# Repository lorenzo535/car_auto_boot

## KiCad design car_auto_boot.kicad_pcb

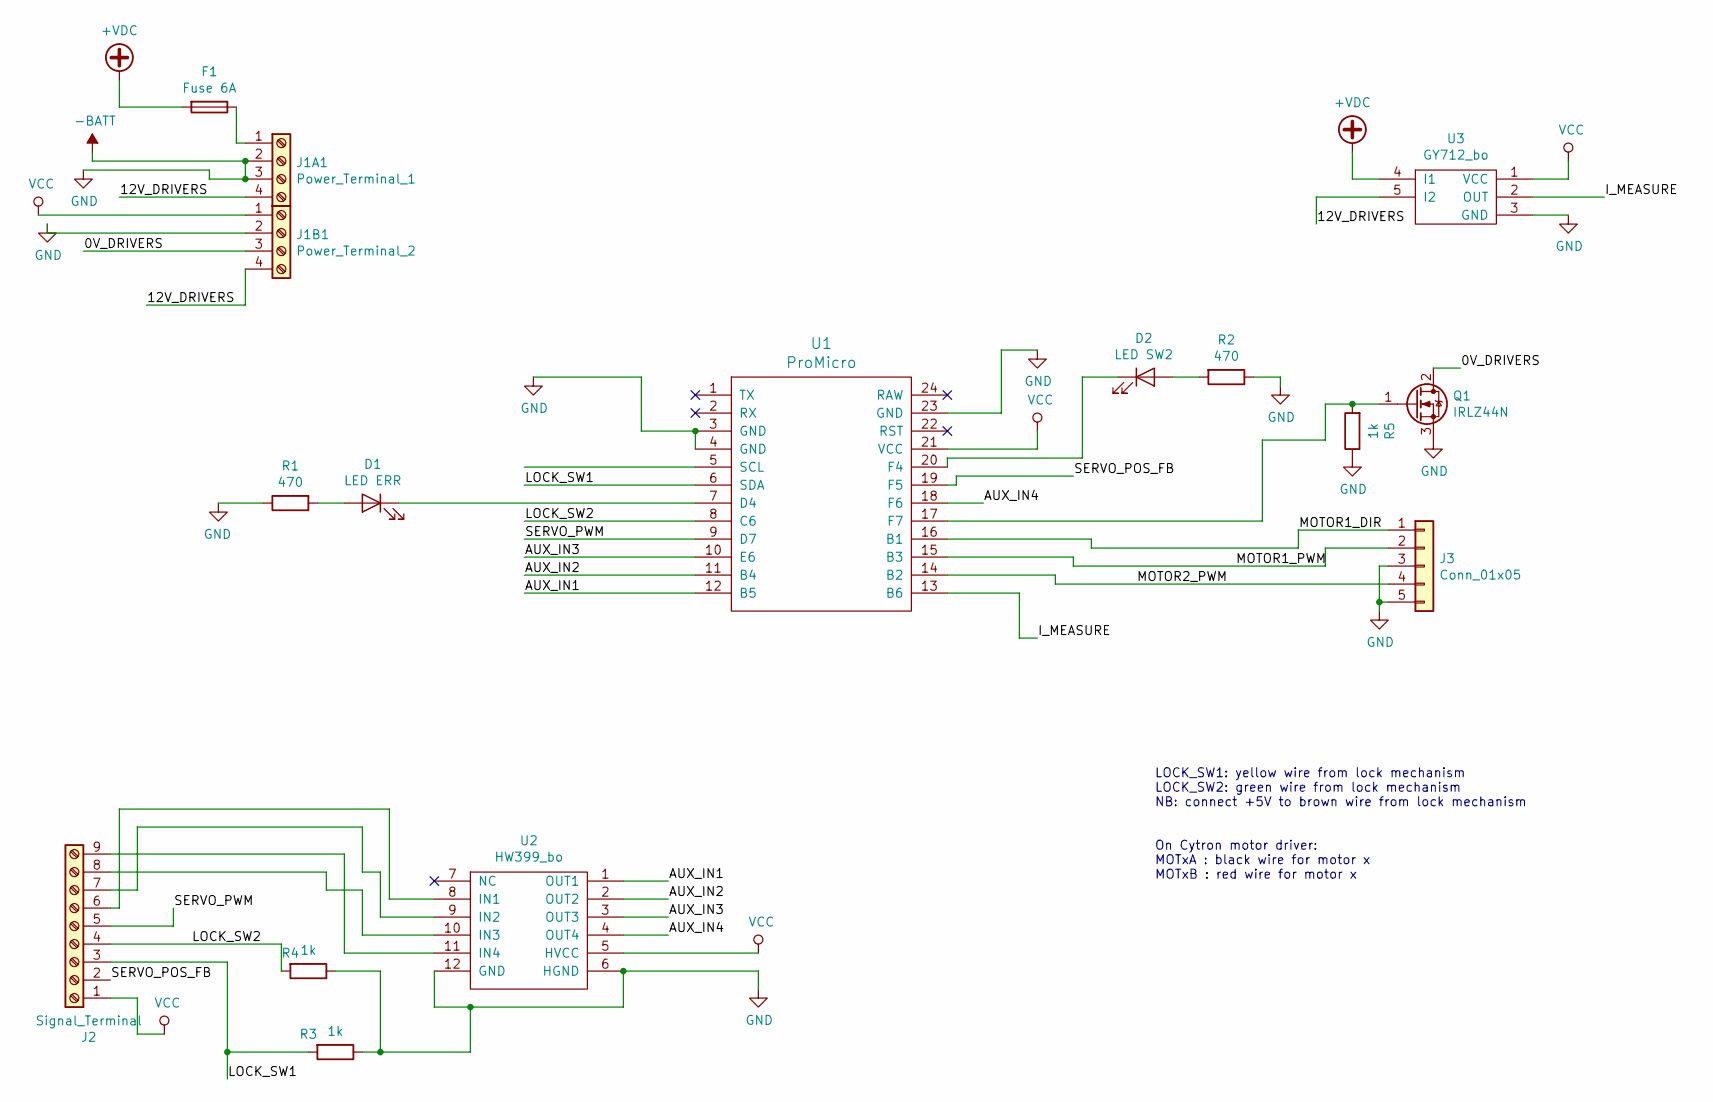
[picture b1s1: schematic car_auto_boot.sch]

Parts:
D1: LED ERR; LED_D3.0mm
D2: LED SW2; LED_D3.0mm
F1: Fuse 6A; Fuseholder5x20_horiz_SemiClosed_Casing10x25mm
J1A1: Power_Terminal_1; TerminalBlock_bornier-4_P5.08mm
J1B1: Power_Terminal_2; TerminalBlock_bornier-4_P5.08mm
J2: Signal_Terminal; TerminalBlock_Phoenix_MPT-2.54mm_9pol
J3: Conn_01x05; TerminalBlock_Phoenix_MPT-2.54mm_5pol
Q1: IRLZ44N; TO-220-3_Vertical
R1, R2: 470; R_Axial_DIN0207_L6.3mm_D2.5mm_P7.62mm_Horizontal
R3, R4, R5: 1k; R_Axial_DIN0207_L6.3mm_D2.5mm_P7.62mm_Horizontal
U1: ProMicro
U2: HW399_bo; HW399_BO
U3: GY712_bo; GY712_BO

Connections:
+VDC: F1.2, U3.4 (I1)
-BATT: J1A1.2, J1A1.3, J1B1.2, J3.3, J3.5, Q1.3 (S), R1.1, R2.1, R3.1, R4.1, R5.1, U1.3 (GND), U1.4 (GND), U1.23 (GND), U2.6 (HGND), U2.12 (GND), U3.3 (GND)
/0V_DRIVERS: J1B1.3, Q1.2 (D)
/12V_DRIVERS: J1A1.4, J1B1.4, U3.5 (I2)
/AUX_IN1: U1.12 (B5), U2.1 (OUT1)
/AUX_IN2: U1.11 (B4), U2.2 (OUT2)
/AUX_IN3: U1.10 (E6), U2.3 (OUT3)
/AUX_IN4: U1.18 (F6), U2.4 (OUT4)
/I_MEASURE: U1.13 (B6), U3.2 (OUT)
/LOCK_SW1: J2.3, R3.2, U1.6 (SDA)
/LOCK_SW2: J2.4, R4.2, U1.8 (C6)
/MOTOR1_DIR: J3.1, U1.16 (B1)
/MOTOR1_PWM: J3.2, U1.15 (B3)
/MOTOR2_PWM: J3.4, U1.14 (B2)
/SERVO_POS_FB: J2.2, U1.19 (F5)
/SERVO_PWM: J2.5, U1.9 (D7)
unnamed: D1.1 (K), U1.7 (D4)
unnamed: D1.2 (A), R1.2
unnamed: D2.1 (K), U1.20 (F4)
unnamed: D2.2 (A), R2.2
unnamed: F1.1, J1A1.1
unnamed: J2.6, U2.8 (IN1)
unnamed: J2.7, U2.9 (IN2)
unnamed: J2.8, U2.10 (IN3)
unnamed: J2.9, U2.11 (IN4)
unnamed: Q1.1 (G), R5.2, U1.17 (F7)
VCC: J1B1.1, J2.1, U1.21 (VCC), U2.5 (HVCC), U3.1 (VCC)

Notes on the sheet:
LOCK_SW1: yellow wire from lock mechanism LOCK_SW2: green wire from lock mechanism NB: connect +5V to brown wire from lock mechanism On Cytron motor driver: MOTxA : black wire for motor x MOTxB : red wire for motor x

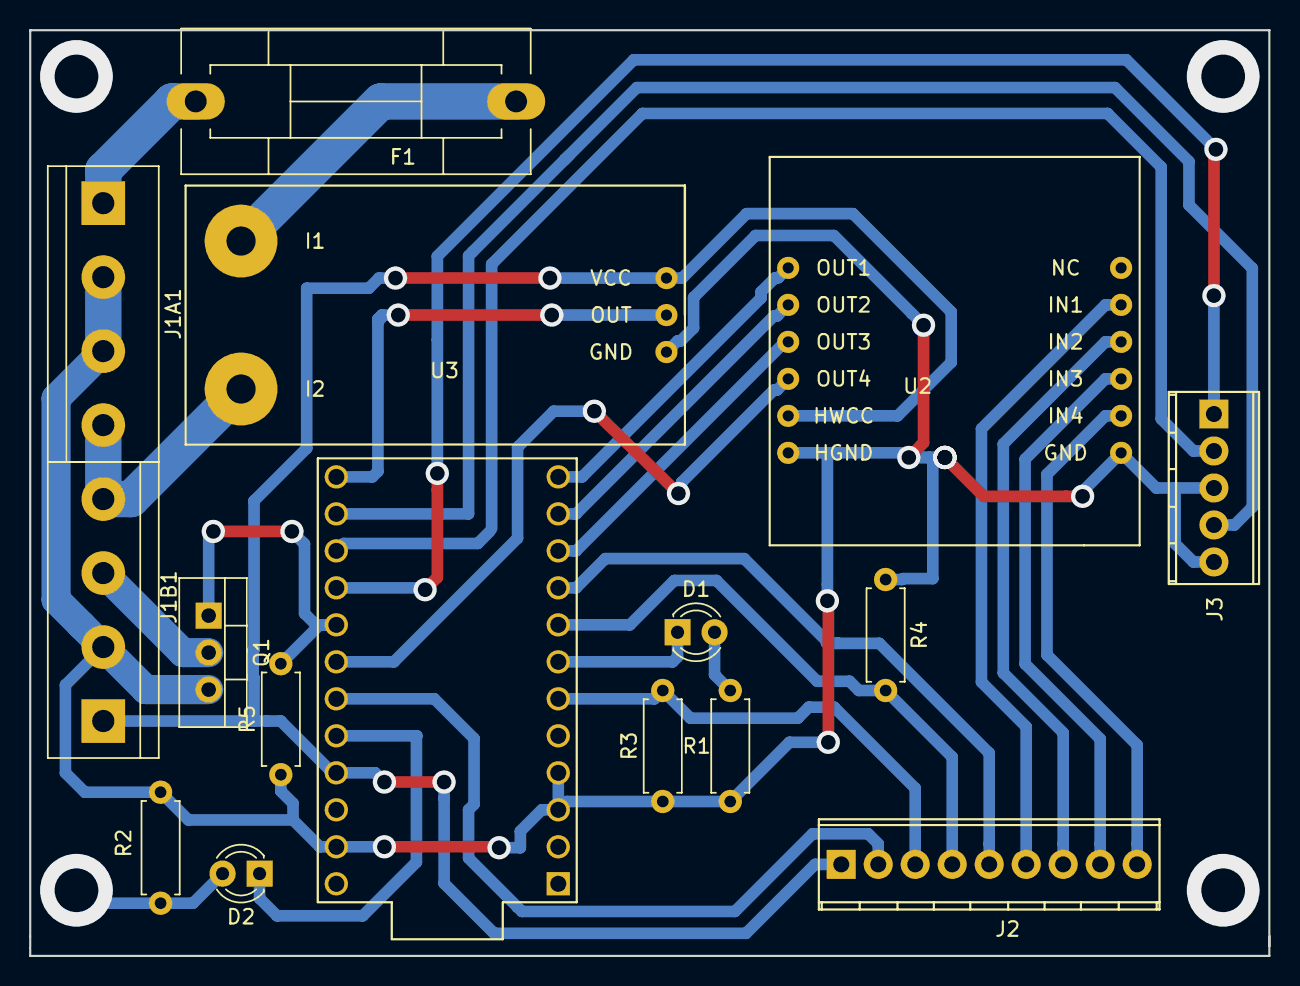
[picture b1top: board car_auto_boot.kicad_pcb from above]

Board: 2 copper layers, 85.1 x 63.5 mm, 16 parts (0 on the bottom side), 27 nets.

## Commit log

2019-01-05 first version OK , correct PWM line , as tested on car
2019-01-07 version with mosfet
